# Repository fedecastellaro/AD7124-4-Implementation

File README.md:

## AD7124 24 BITS ADC

Implementation for a AD7124-4 24 bits sigma delta ADC. 

# Application Circuit
As a simple application circuit you can guide yourself with the following one:

This is a pressure sensor limited in bandwith (fc = 250Hz) connected directly to the AIN0 of the ADC. All the others inputs of the ADC were shorted to ground because they not used in this example. 

# Code

Before starting, **please read the Disclaimer**.

You'll need to include in your directory the following files:
- ad7124.c
- ad7124.h
- ad7124_regs.c
- ad7124_regs.h

You can find them in the "software" folder.

# Setup:

Use the following lines to configure your AD7124:

- Ad7124Chip_setConfig     (SETUP_0, RefInternal, Pga1, TRUE, BurnoutOff);
- Ad7124Chip_setChannel    (CHANNEL_0, SETUP_0, AIN0Input, AIN1Input, FALSE);
- Ad7124Chip_setAdcControl (StandbyMode, FullPower, TRUE, InternalClk);

# Take a Sample:

- uint32_t sample = Ad7124Chip_read(CHANNEL_0);

You can find a full working code for a LPC1769 Cortex®-M3 microcontroler in the folder "AD7124_MYFUNC"

## Disclaimer:

Please take in mind that all the **functions in the file ad7124.c where modified to be used with a LPC1769 Cortex®-M3 microcontroler** using the LPCOpen standard APIs.
This means that in order to make it work in your uC **you'll need to set up your own SPI communication functions**.

In this code, you'll need to adapt the function:
  - Chip_SSP_RWFrames_Blocking() 

And the Macros:
  - SSP_CS_LOW
  - SSP_CS_HIGH

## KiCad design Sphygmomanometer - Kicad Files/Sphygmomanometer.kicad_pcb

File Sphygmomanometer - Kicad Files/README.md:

# Sphygmomanometer Design

## Kicad files

This are the files of a very simple but effective Sphygmomanometer.
It uses a MP3V5050GP as a pressure sensor, a 2nd order Butterworth low pass filter, a LPC1769 dev-board as uC, and a LCD 16x2 to present values.

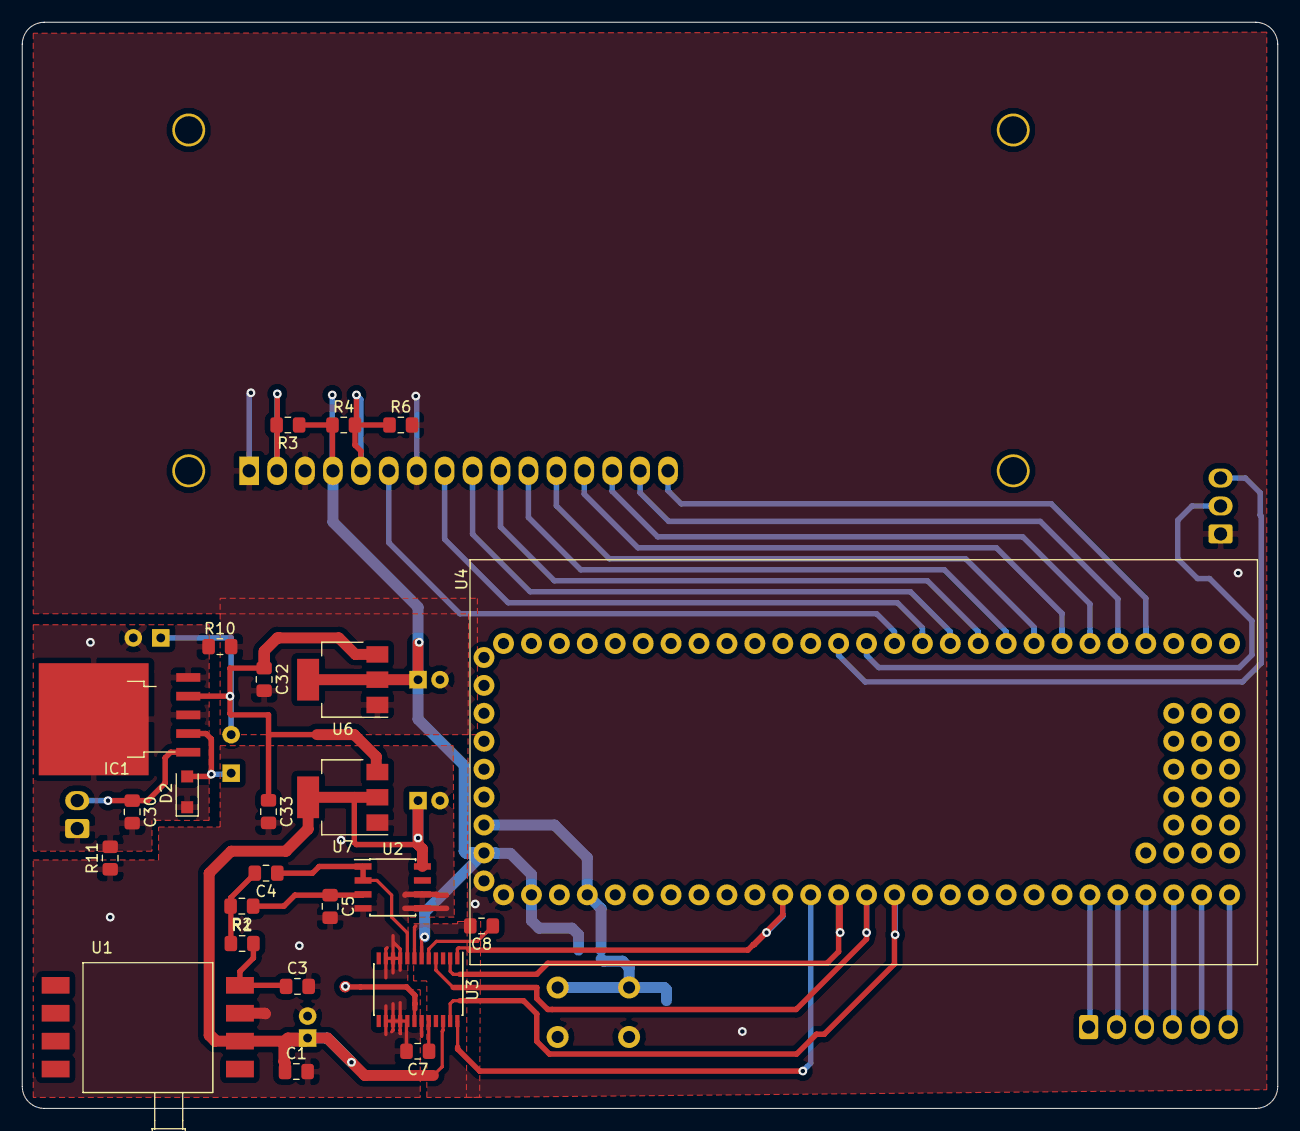
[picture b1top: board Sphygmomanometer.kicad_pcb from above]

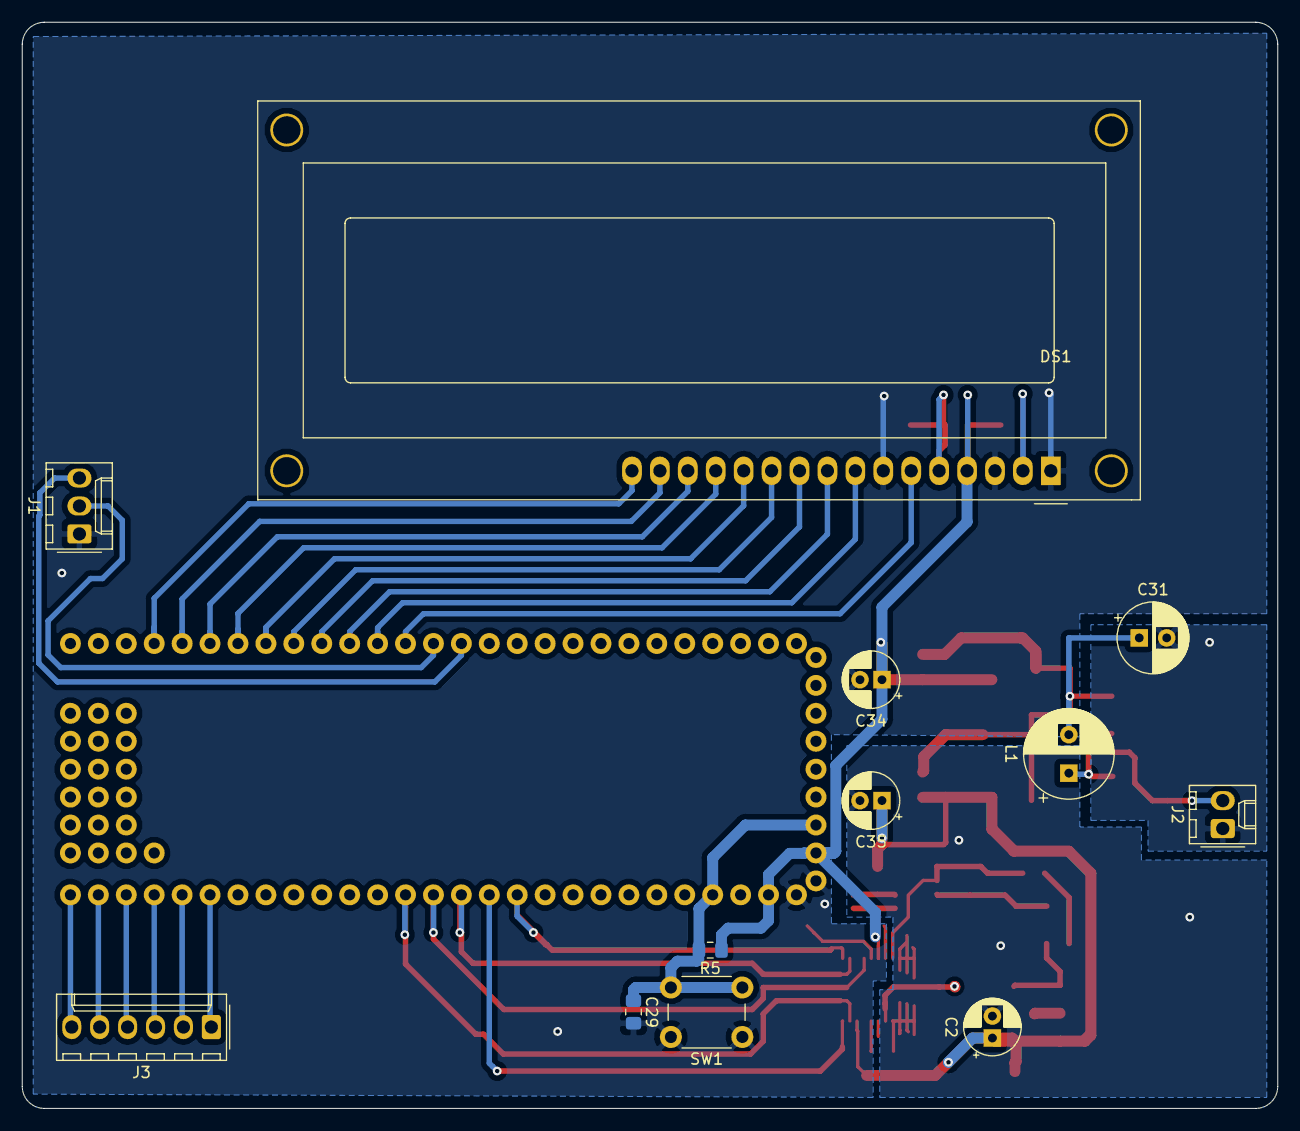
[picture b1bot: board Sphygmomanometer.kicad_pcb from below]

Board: 2 copper layers, 114.2 x 98.8 mm, 36 parts (12 on the bottom side), 40 nets.

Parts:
C1, C7, C8: 0.1uF; C_0805_2012Metric_Pad1.15x1.40mm_HandSolder
C2: 1.0uF; CP_Radial_D5.0mm_P2.00mm
C3: 470pF; C_0805_2012Metric_Pad1.15x1.40mm_HandSolder
C4, C5: 10nF; C_0805_2012Metric_Pad1.15x1.40mm_HandSolder
C29, C30, C32, C33: 100nF; C_0805_2012Metric_Pad1.15x1.40mm_HandSolder
C31: 220uF; CP_Radial_D6.3mm_P2.50mm
C34, C35: 10uF; CP_Radial_D5.0mm_P2.00mm
D2: MBR120E5FT1G; D_SOD-123F
DS1: HY1602E; WC1602A
IC1: LM2575-5.0; TO-252-5_TabPin3_arreglado
J1: Comunicacion con PC; Molex_KK-254_AE-6410-03A_1x03_P2.54mm_Vertical
J2: bateria; Molex_KK-254_AE-6410-02A_1x02_P2.54mm_Vertical
J3: AUX; Molex_KK-254_AE-6410-06A_1x06_P2.54mm_Vertical
L1: 220uH; CP_Radial_D8.0mm_P3.50mm
R1, R2: 33K; R_0805_2012Metric_Pad1.15x1.40mm_HandSolder
R3: 470R; R_0805_2012Metric_Pad1.15x1.40mm_HandSolder
R4, R6: 1K; R_0805_2012Metric_Pad1.15x1.40mm_HandSolder
R5: 100k; R_0805_2012Metric_Pad1.15x1.40mm_HandSolder
R10, R11: 0; R_0805_2012Metric_Pad1.15x1.40mm_HandSolder
SW1: RESET; SW_PUSH_6mm
U1: MP3V5050GP; SOP-8
U2: MCP6002-xSN; SOIC-8_3.9x4.9mm_P1.27mm
U3: AD7124; TSSOP-24_4.4x7.8mm_P0.65mm
U4: LPCXPRESSO1769; LPC1769_Target_RevB
U6: NCP1117ST33T3G; SOT-223-3_TabPin2
U7: LDL1117S30R; SOT-223-3_TabPin2

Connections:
+BATT: C30.1, IC1.1, J2.2
/MicroControlador/LCD_DB0: DS1.9, U4.44
/MicroControlador/LCD_DB1: DS1.10, U4.45
/MicroControlador/LCD_DB2: DS1.11, U4.46
/MicroControlador/LCD_DB3: DS1.12, U4.47
/MicroControlador/LCD_DB4: DS1.13, U4.48
/MicroControlador/LCD_DB5: DS1.14, U4.49
/MicroControlador/LCD_DB6: DS1.15, U4.50
/MicroControlador/LCD_DB7: DS1.16, U4.51
/MicroControlador/LCD_ENABLE: DS1.8, U4.43
/MicroControlador/LCD_RS: DS1.6, U4.42
/MicroControlador/RESET: C29.1, R5.2, SW1.2, U4.4, U4.76
/MicroControlador/SPI_CS: U3.4, U4.14
/MicroControlador/SPI_MISO: U3.24, U4.12
/MicroControlador/SPI_MOSI: U3.1, U4.11
/MicroControlador/SPI_SCK: U3.2, U4.13
/MicroControlador/UART0_RXD: J1.2, U4.41
/MicroControlador/UART0_TXD: J1.3, U4.40
/MicroControlador/~SYNC: U3.23, U4.15
GND: C30.2, C31.2, D2.1, IC1.3, IC1.5, J2.1, R10.1, R11.2
GNDA: C1.2, C2.2, C3.2, C5.2, C7.2, C33.2, C35.2, R11.1, U1.3, U2.4, U2.5, U2.6, U3.9, U3.10, U3.11, U3.14, U3.15, U3.16, U3.17, U3.19, U7.1
GNDD: C8.2, C29.2, C32.2, C34.2, DS1.1, DS1.3, DS1.7, J1.1, R6.2, R10.2, SW1.1, U3.7, U4.1, U4.74, U6.1
unnamed: C3.1, R1.2, U1.4
unnamed: C4.1, U2.1, U2.2, U3.8
unnamed: C4.2, R1.1, R2.2
unnamed: C5.1, R2.1, U2.3
unnamed: C7.1, U3.20
unnamed: C8.1, U3.5
unnamed: D2.2, IC1.2, L1.1
unnamed: DS1.2, R3.2
unnamed: DS1.5, R4.2, R6.1
unnamed: J3.1, U4.22
unnamed: J3.2, U4.23
unnamed: J3.3, U4.24
unnamed: J3.4, U4.25
unnamed: J3.5, U4.26
unnamed: J3.6, U4.27
VCC: C31.1, C32.1, C33.1, IC1.4, L1.2, U6.3, U7.3
VDD: C34.1, DS1.4, R3.1, R4.1, R5.1, U3.6, U4.2, U4.75, U6.2
VDDA: C1.1, C2.1, C35.1, U1.2, U2.8, U3.22, U7.2

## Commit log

2021-11-14 README
2021-11-15 README.md
2021-11-15 Data update
2021-11-15 changed main
2021-11-15 Added kicad files of the proyect
2021-11-15 Added 3D PCB preview
